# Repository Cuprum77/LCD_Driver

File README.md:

# LCD Driver Project

This repository contains my attempt at creating a "universal" driver board that fits most of the new 40 pin LCDs from China. These new LCDs all utilize a 40 pin flat flex cable, and utilize the ST7701 driver IC. 
This means that they are rather simple RGB devices, not too unlike the old VGA standard. 
The main goal however, is to have a board that does not require any system drivers, and utilize the standard connectors that are available on most SBCs, such as the Raspberry Pi, as well as most laptops and desktops.

## Table of contents
- [Supported LCDs](#supported-lcds)
- [Project layout](#project-layout)
- [License](#license)

## Supported LCDs

This table lists the LCDs that I have bought and tested with the driver board.

| Format | Size  | Resolution | Driver IC | Touch | Link      | Additional notes |
| ------ | ----- | ---------- | --------- | ----- | --------- | ---------------- |
| Bar    | 3.99" | 400x960    | ST7701    | Yes   | [AliExpress](https://www.aliexpress.com/item/1005005622337201.html) | |
| Square | 3.95" | 480x480    | ST7701    | Yes   | [AliExpress](https://www.aliexpress.com/item/1005005230886441.html) | NOT FULLY TESTED YET |

Alternatively, any other board that uses the ST7701 driver IC and with the following [pinout](./resources/PINOUT.md) should work with the driver board. However, you must generate a new ROM file for the FPGA.

## Project layout
- [UVVM_Light](https://github.com/UVVM/UVVM_Light) - The UVVM framework
- [bitfiles](bitfiles/) - FPGA bitfiles
- [edid](edid/) - EDID files for the LCDs
- [hardware](hardware/) - The KiCad project files for the driver boards
- [resources](resources/) - Resources for the project, such as datasheets
- [rom](rom/) - The ROM files for the FPGA projects
- [sim](sim/) - The UVVM testbenches for the driver boards
- [software](software/) - The software for the driver boards
- [vivado-library](https://github.com/Digilent/vivado-library/) - The Vivado library files for the driver boards

## License
This project is licensed under CERN Open Hardware License Version 2 - Strong Reciprocity (CERN-OHL-S-2.0). See [LICENSE](LICENSE) for more details.
Note that some files in this repository may be licensed under different licenses. Please check the respective files for more information.

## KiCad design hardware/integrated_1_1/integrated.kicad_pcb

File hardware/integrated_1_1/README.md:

# Integrated Solution Rev 1.1

## Introduction

Even smaller than the previous revision, this design is a complete redesign of the previous, and implements fixes for the critical errors in the previous design. This design is still in the prototype phase and is not ready for production.

This is a PCB that integrates everything needed to drive the display. It is designed to sit on the back of the display without interfering with the display frame. It is specifically designed for the pinout of the newer non-standard displays that have come out of China in the recent years. Specifically those that support the RGB666 interface.

This design utilizes a Spartan 6 FPGA to drive the display. This was chosen over dedicated ASICs due to cost and adaptability. This should allow me to add features such as a splash screen or other custom features that are not possible with a dedicated ASIC.

## Features
- Spartan 6 FPGA [^1]
- DVI Input [^2]
- RP2040 microcontroller
- USB-C [^3] [^4]
- Backlight driver with dimming control
- LCD connector

[^1]: XC6SLX9-TQG144
[^2]: The DVI input is over a HDMI-like connector. This is due to licensing issues with the HDMI standard that I cannot afford to pay for. Any reference to HDMI in this project is purely for the sake of simplicity and is not meant to imply that this project is HDMI compatible.
[^3]: Does not support PD.
[^4]: Limited to USB 1.1 speeds. This is limited by the RP2040 which handles the USB interface.

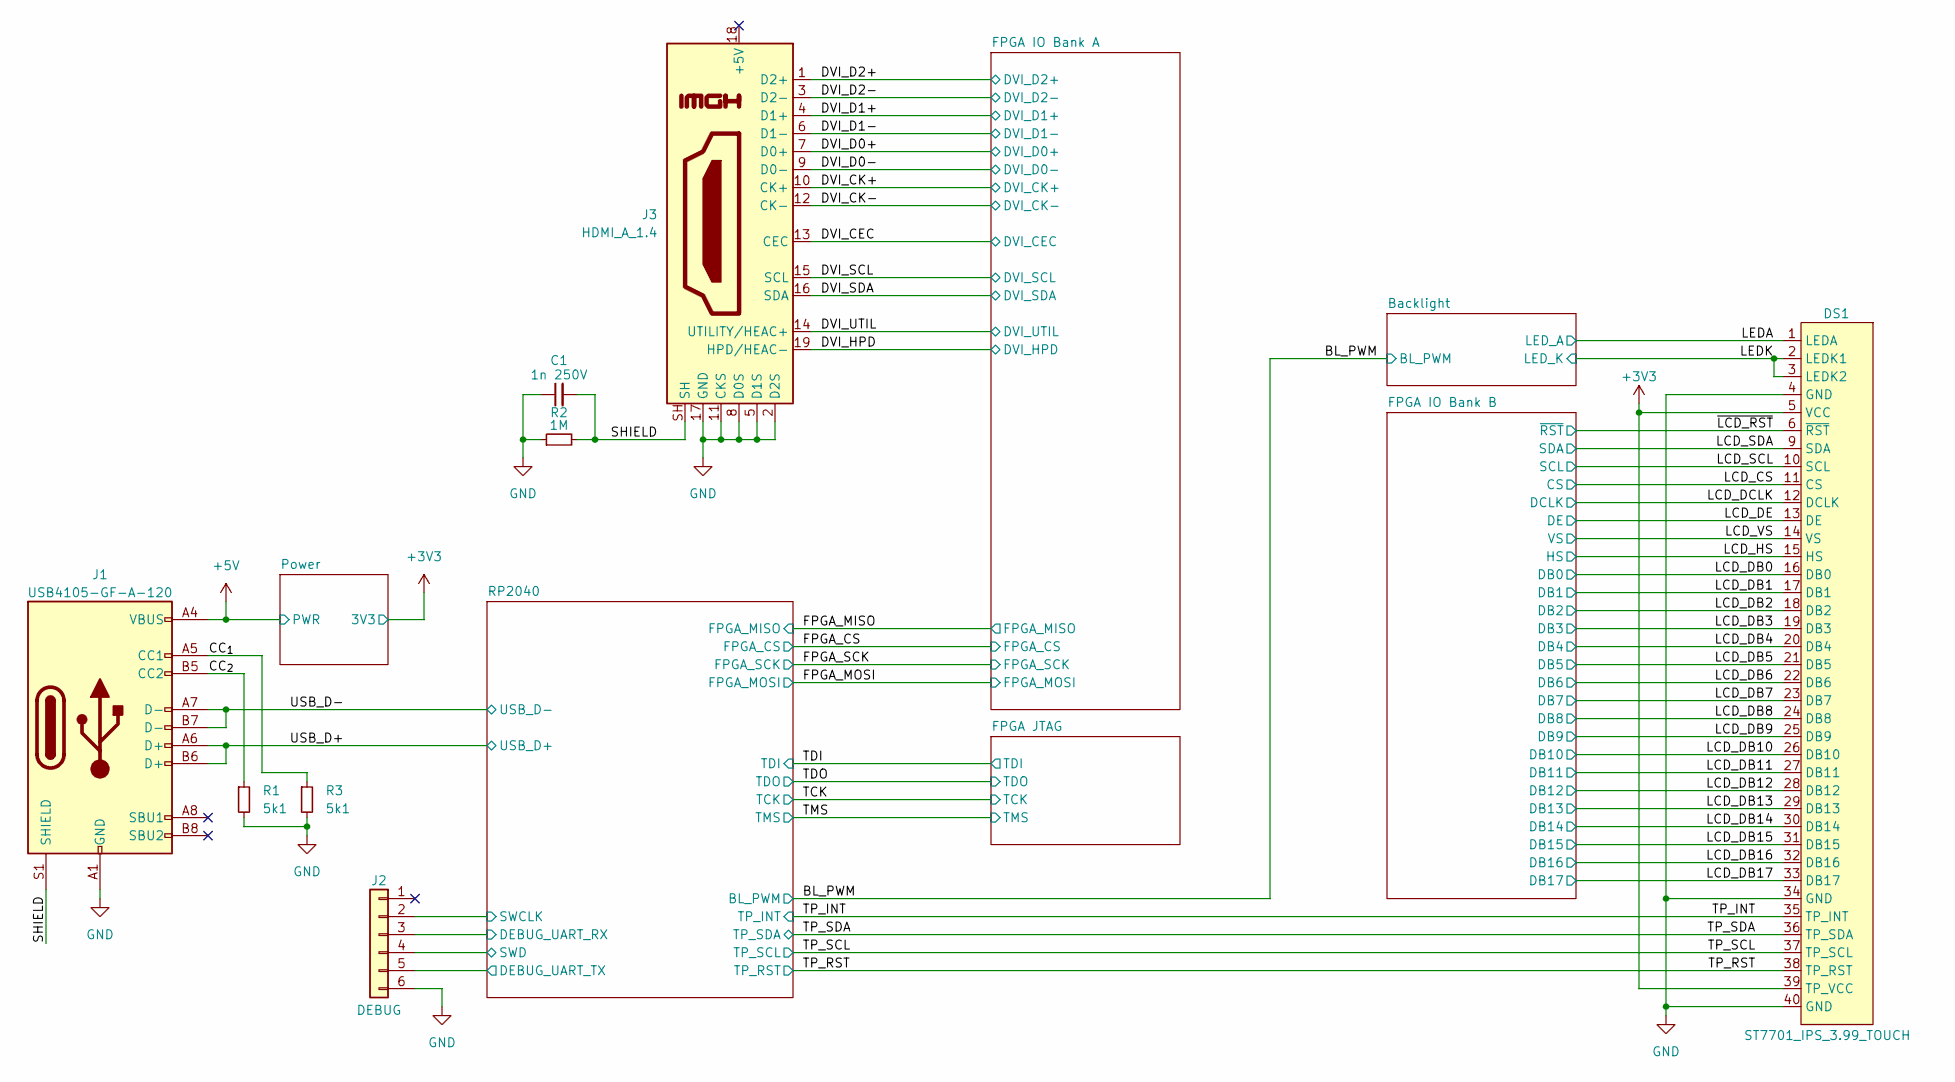
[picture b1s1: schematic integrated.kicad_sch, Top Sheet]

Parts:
C1: 1n 250V; C_0603_1608Metric
DS1: ST7701_IPS_3.99_TOUCH; GCT_FFC2B35-40-G_REVA2_INV
J1: USB4105-GF-A-120; CONN_217182-0001_MOL
J2: DEBUG; Paw-Connect_RevB_TC2030-IDC-NL_2x03_P1.27mm_Vertical
J3: HDMI_A_1.4; MOLEX_476591102
R1, R3: 5k1; R_0402_1005Metric
R2: 1M; R_0402_1005Metric

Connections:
+3V3: DS1.5 (VCC), DS1.39 (TP_VCC); also elsewhere on the board
+5V: J1.A4 (VBUS), J1.A9 (VBUS), J1.B4 (VBUS), J1.B9 (VBUS); also elsewhere on the board
/CC_{1}: J1.A5 (CC1), R3.1
/CC_{2}: J1.B5 (CC2), R1.1
/DVI_CEC: J3.13 (CEC); also elsewhere on the board
/DVI_CK+: J3.10 (CK+); also elsewhere on the board
/DVI_CK-: J3.12 (CK-); also elsewhere on the board
/DVI_D0+: J3.7 (D0+); also elsewhere on the board
/DVI_D0-: J3.9 (D0-); also elsewhere on the board
/DVI_D1+: J3.4 (D1+); also elsewhere on the board
/DVI_D1-: J3.6 (D1-); also elsewhere on the board
/DVI_D2+: J3.1 (D2+); also elsewhere on the board
/DVI_D2-: J3.3 (D2-); also elsewhere on the board
/DVI_HPD: J3.19 (HPD/HEAC-); also elsewhere on the board
/DVI_SCL: J3.15 (SCL); also elsewhere on the board
/DVI_SDA: J3.16 (SDA); also elsewhere on the board
/LCD_CS: DS1.11 (CS); also elsewhere on the board
/LCD_DB0: DS1.16 (DB0); also elsewhere on the board
/LCD_DB1: DS1.17 (DB1); also elsewhere on the board
/LCD_DB2: DS1.18 (DB2); also elsewhere on the board
/LCD_DB3: DS1.19 (DB3); also elsewhere on the board
/LCD_DB4: DS1.20 (DB4); also elsewhere on the board
/LCD_DB5: DS1.21 (DB5); also elsewhere on the board
/LCD_DB6: DS1.22 (DB6); also elsewhere on the board
/LCD_DB7: DS1.23 (DB7); also elsewhere on the board
/LCD_DB8: DS1.24 (DB8); also elsewhere on the board
/LCD_DB9: DS1.25 (DB9); also elsewhere on the board
/LCD_DB10: DS1.26 (DB10); also elsewhere on the board
/LCD_DB11: DS1.27 (DB11); also elsewhere on the board
/LCD_DB12: DS1.28 (DB12); also elsewhere on the board
/LCD_DB13: DS1.29 (DB13); also elsewhere on the board
/LCD_DB14: DS1.30 (DB14); also elsewhere on the board
/LCD_DB15: DS1.31 (DB15); also elsewhere on the board
/LCD_DB16: DS1.32 (DB16); also elsewhere on the board
/LCD_DB17: DS1.33 (DB17); also elsewhere on the board
/LCD_DCLK: DS1.12 (DCLK); also elsewhere on the board
/LCD_DE: DS1.13 (DE); also elsewhere on the board
/LCD_HS: DS1.15 (HS); also elsewhere on the board
/LCD_SCL: DS1.10 (SCL); also elsewhere on the board
/LCD_SDA: DS1.9 (SDA); also elsewhere on the board
/LCD_VS: DS1.14 (VS); also elsewhere on the board
/LEDA: DS1.1 (LEDA); also elsewhere on the board
/LEDK: DS1.2 (LEDK1), DS1.3 (LEDK2); also elsewhere on the board
/RP2040/DEBUG_UART_RX: J2.3; also elsewhere on the board
/RP2040/DEBUG_UART_TX: J2.5; also elsewhere on the board
/RP2040/SWCLK: J2.2; also elsewhere on the board
/RP2040/SWD: J2.4; also elsewhere on the board
/SHIELD: C1.2, J1.S1 (SHIELD), J3.SH, J3.SH1 (SH), J3.SH2 (SH), J3.SH3 (SH), R2.2
/TP_INT: DS1.35 (TP_INT); also elsewhere on the board
/TP_RST: DS1.38 (TP_RST); also elsewhere on the board
/TP_SCL: DS1.37 (TP_SCL); also elsewhere on the board
/TP_SDA: DS1.36 (TP_SDA); also elsewhere on the board
/USB_D+: J1.A6 (D+), J1.B6 (D+); also elsewhere on the board
/USB_D-: J1.A7 (D-), J1.B7 (D-); also elsewhere on the board
/~LCD_RST: DS1.6 (~RST); also elsewhere on the board
GND: C1.1, DS1.4 (GND), DS1.34 (GND), DS1.40 (GND), DS1.S1 (GND), DS1.S2 (GND), J1.A1 (GND), J1.A12 (GND), J1.B1 (GND), J1.B12 (GND), J2.6, J3.2 (D2S), J3.5 (D1S), J3.8 (D0S), J3.11 (CKS), J3.14 (UTILITY/HEAC+), J3.17 (GND), R1.2, R2.1, R3.2; also elsewhere on the board

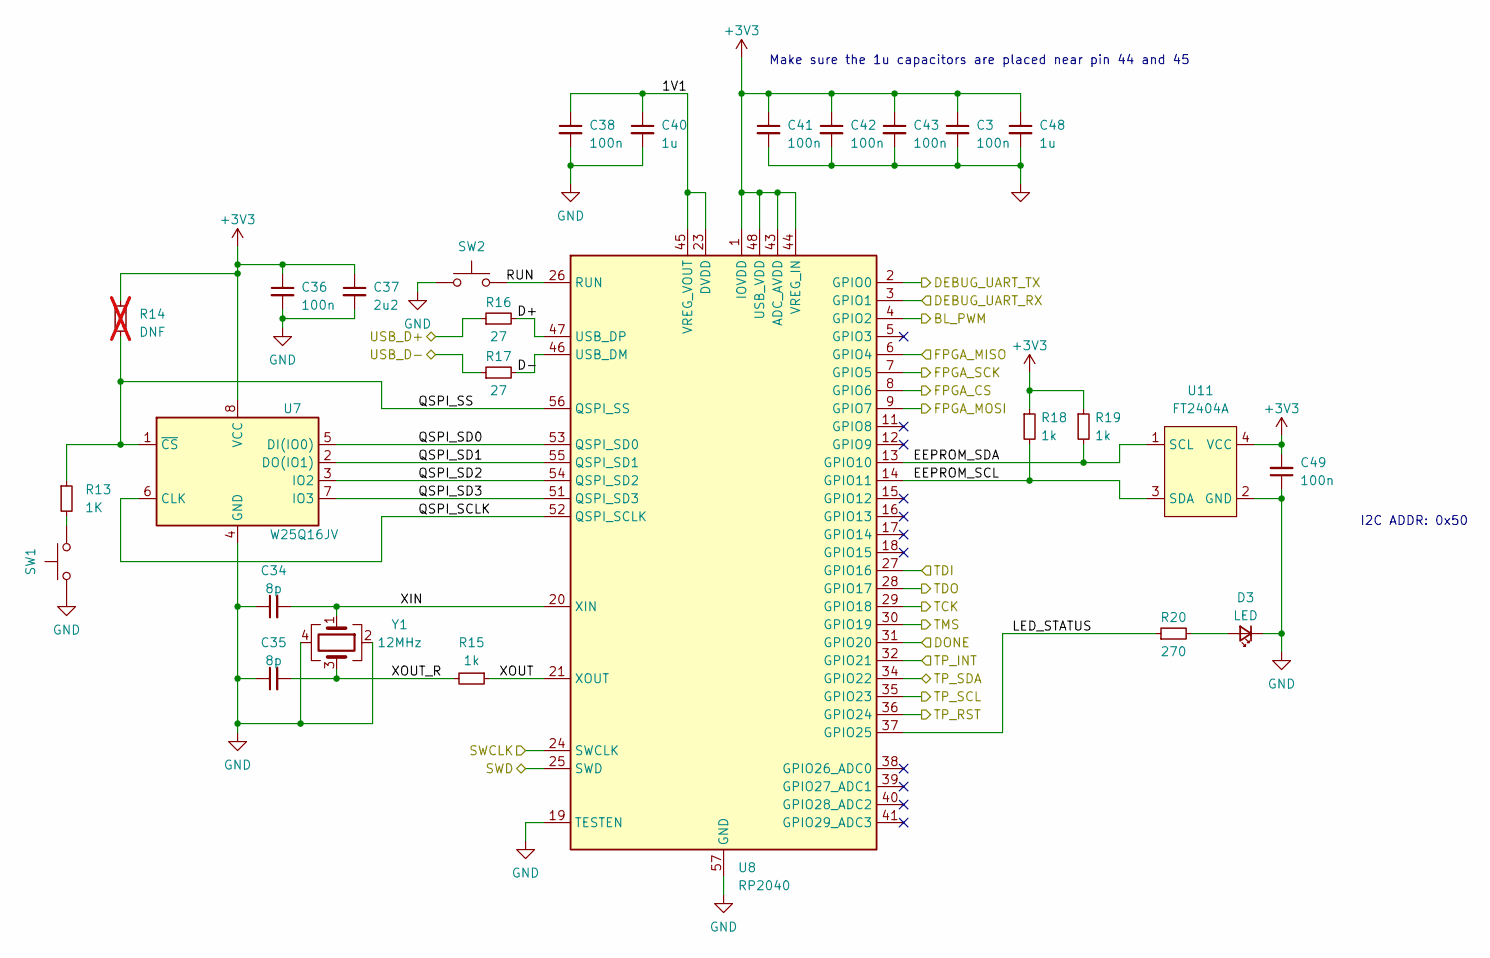
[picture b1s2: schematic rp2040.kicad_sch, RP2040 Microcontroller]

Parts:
C3, C36, C38, C41, C42, C43, C49: 100n; C_0402_1005Metric
C34, C35: 8p; C_0402_1005Metric
C37: 2u2; C_0402_1005Metric
C40, C48: 1u; C_0402_1005Metric
D3: LED; D_0805_2012Metric
R13: 1K; R_0402_1005Metric
R14: DNF; R_0402_1005Metric; not fitted
R15, R18, R19: 1k; R_0402_1005Metric
R16, R17: 27; R_0402_1005Metric
R20: 270; R_0402_1005Metric
SW1, SW2: DNF; PTS636 SM25J SMTR LFS
U7: W25Q16JV; W25Q16JVUXIQ TR
U8: RP2040; QFN-56-1EP_7x7mm_P0.4mm_EP3.2x3.2mm
U11: FT2404A; SOT-23-5
Y1: 12MHz; ECS120836CKMTR3

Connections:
+3V3: C3.1, C36.1, C37.1, C41.1, C42.1, C43.1, C48.1, C49.2, R14.2, R18.1, R19.1, U7.8 (VCC), U8.1 (IOVDD), U8.10 (IOVDD), U8.22 (IOVDD), U8.33 (IOVDD), U8.42 (IOVDD), U8.43 (ADC_AVDD), U8.44 (VREG_IN), U8.48 (USB_VDD), U8.49 (IOVDD), U11.4 (VCC); also elsewhere on the board
/BL_PWM: U8.4 (GPIO2); also elsewhere on the board
/FPGA_CS: U8.8 (GPIO6); also elsewhere on the board
/FPGA_MISO: U8.6 (GPIO4); also elsewhere on the board
/FPGA_MOSI: U8.9 (GPIO7); also elsewhere on the board
/FPGA_SCK: U8.7 (GPIO5); also elsewhere on the board
/RP2040/1V1: C38.1, C40.1, U8.23 (DVDD), U8.45 (VREG_VOUT), U8.50 (DVDD)
/RP2040/D+: R16.2, U8.47 (USB_DP)
/RP2040/D-: R17.2, U8.46 (USB_DM)
/RP2040/DEBUG_UART_RX: U8.3 (GPIO1); also elsewhere on the board
/RP2040/DEBUG_UART_TX: U8.2 (GPIO0); also elsewhere on the board
/RP2040/DONE: U8.31 (GPIO20)
/RP2040/EEPROM_SCL: R18.2, U8.14 (GPIO11), U11.3 (SDA)
/RP2040/EEPROM_SDA: R19.2, U8.13 (GPIO10), U11.1 (SCL)
/RP2040/LED_STATUS: R20.1, U8.37 (GPIO25)
/RP2040/QSPI_SCLK: U7.6 (CLK), U8.52 (QSPI_SCLK)
/RP2040/QSPI_SD0: U7.5 (DI(IO0)), U8.53 (QSPI_SD0)
/RP2040/QSPI_SD1: U7.2 (DO(IO1)), U8.55 (QSPI_SD1)
/RP2040/QSPI_SD2: U7.3 (IO2), U8.54 (QSPI_SD2)
/RP2040/QSPI_SD3: U7.7 (IO3), U8.51 (QSPI_SD3)
/RP2040/QSPI_SS: R13.1, R14.1, U7.1 (~CS), U8.56 (QSPI_SS)
/RP2040/RUN: SW2.2, U8.26 (RUN)
/RP2040/SWCLK: U8.24 (SWCLK); also elsewhere on the board
/RP2040/SWD: U8.25 (SWD); also elsewhere on the board
/RP2040/XIN: C34.2, U8.20 (XIN), Y1.1
/RP2040/XOUT: R15.1, U8.21 (XOUT)
/RP2040/XOUT_R: C35.2, R15.2, Y1.3
/TCK: U8.29 (GPIO18); also elsewhere on the board
/TDI: U8.27 (GPIO16); also elsewhere on the board
/TDO: U8.28 (GPIO17); also elsewhere on the board
/TMS: U8.30 (GPIO19); also elsewhere on the board
/TP_INT: U8.32 (GPIO21); also elsewhere on the board
/TP_RST: U8.36 (GPIO24); also elsewhere on the board
/TP_SCL: U8.35 (GPIO23); also elsewhere on the board
/TP_SDA: U8.34 (GPIO22); also elsewhere on the board
/USB_D+: R16.1; also elsewhere on the board
/USB_D-: R17.1; also elsewhere on the board
GND: C3.2, C34.1, C35.1, C36.2, C37.2, C38.2, C40.2, C41.2, C42.2, C43.2, C48.2, C49.1, D3.1 (K), SW1.1, SW2.1, U7.4 (GND), U7.9 (GND), U8.19 (TESTEN), U8.57 (GND), U11.2 (GND), Y1.2, Y1.4; also elsewhere on the board
unnamed: D3.2 (A), R20.2
unnamed: R13.2, SW1.2

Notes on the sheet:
I2C ADDR: 0x50
Make sure the 1u capacitors are placed near pin 44 and 45

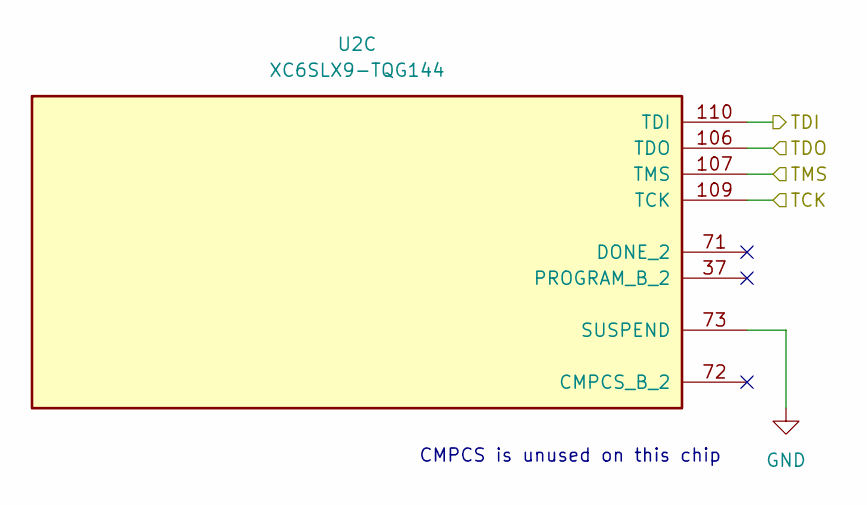
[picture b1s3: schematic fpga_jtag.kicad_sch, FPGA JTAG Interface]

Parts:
U2: XC6SLX9-TQG144; TQFP-144_20x20mm_P0.5mm

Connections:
/TCK: U2.109 (TCK); also elsewhere on the board
/TDI: U2.110 (TDI); also elsewhere on the board
/TDO: U2.106 (TDO); also elsewhere on the board
/TMS: U2.107 (TMS); also elsewhere on the board
GND: U2.73 (SUSPEND); also elsewhere on the board

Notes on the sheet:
CMPCS is unused on this chip

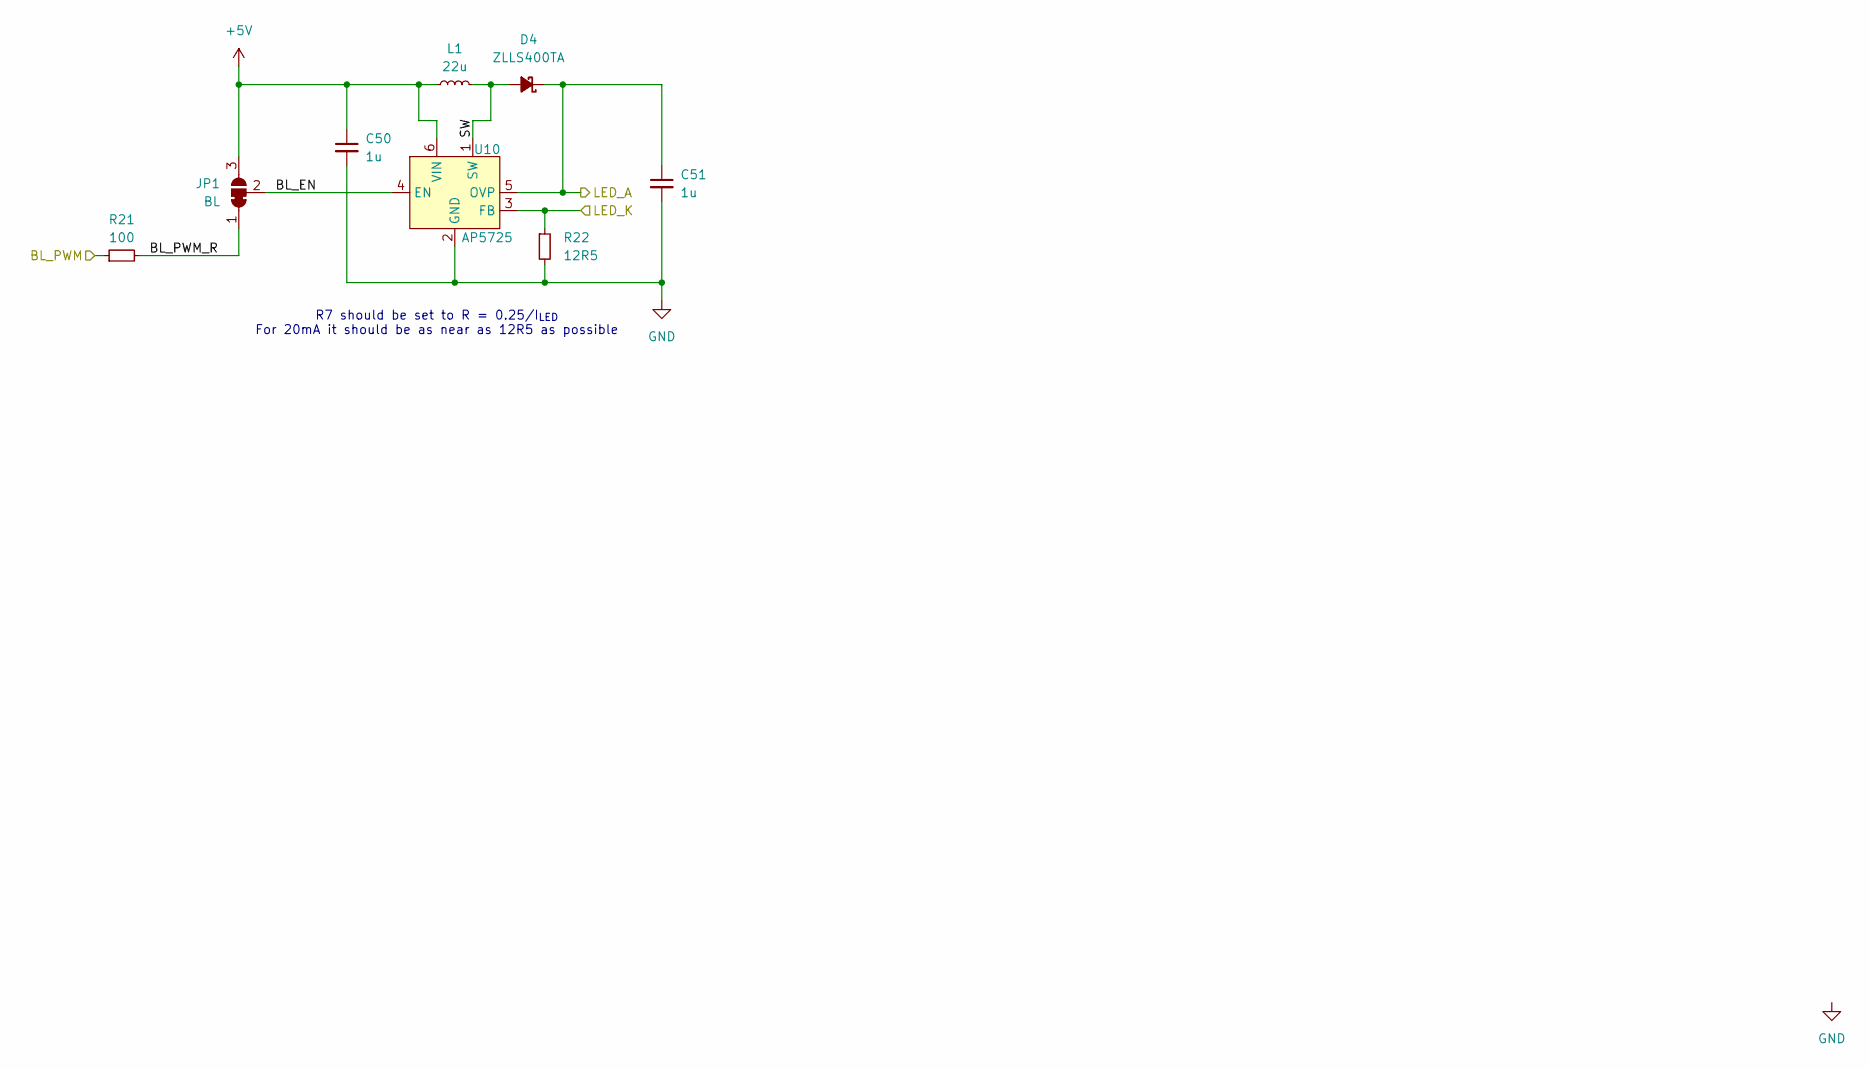
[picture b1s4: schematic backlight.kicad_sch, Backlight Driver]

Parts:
C50: 1u; C_0402_1005Metric
C51: 1u; C_0603_1608Metric
D4: ZLLS400TA; D_SOD-323
JP1: BL; SolderJumper-3_P1.3mm_Bridged12_RoundedPad1.0x1.5mm
L1: 22u; XRNR4012
R21: 100; R_0402_1005Metric
R22: 12R5; R_0603_1608Metric
U10: AP5725; SOT-23-6

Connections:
+5V: C50.1, JP1.3 (B), L1.1, U10.6 (VIN); also elsewhere on the board
/BL_PWM: R21.1; also elsewhere on the board
/Backlight/BL_EN: JP1.2 (C), U10.4 (EN)
/Backlight/BL_PWM_R: JP1.1 (A), R21.2
/Backlight/SW: D4.2 (A), L1.2, U10.1 (SW)
/LEDA: C51.1, D4.1 (K), U10.5 (OVP); also elsewhere on the board
/LEDK: R22.1, U10.3 (FB); also elsewhere on the board
GND: C50.2, C51.2, R22.2, U10.2 (GND); also elsewhere on the board

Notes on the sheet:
R7 should be set to R = 0.25/I_{LED} For 20mA it should be as near as 12R5 as possible

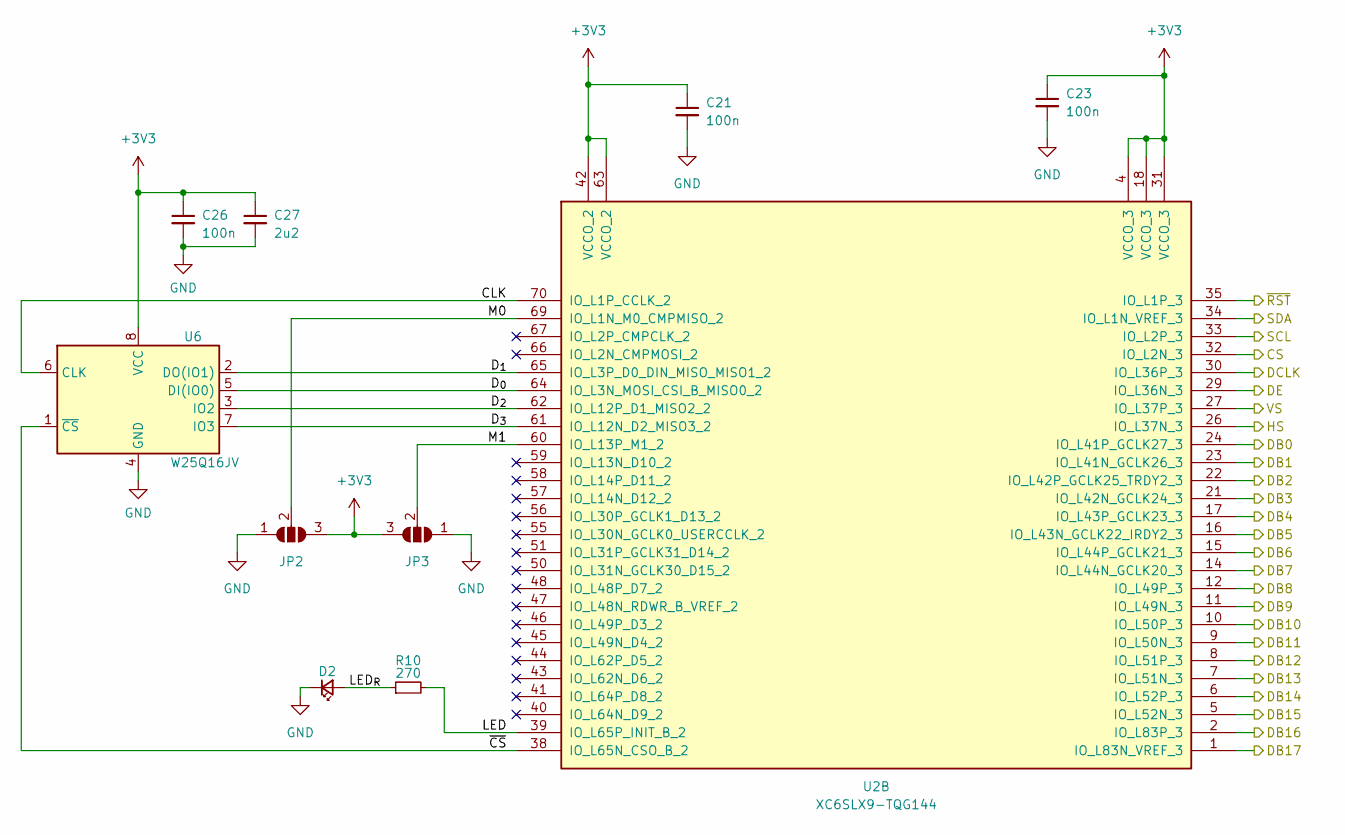
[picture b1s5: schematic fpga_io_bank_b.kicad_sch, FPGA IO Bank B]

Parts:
C21, C23, C26: 100n; C_0402_1005Metric
C27: 2u2; C_0402_1005Metric
D2: LED; D_0805_2012Metric
JP2, JP3: SolderJumper_3_Open; SolderJumper-3_P1.3mm_Open_RoundedPad1.0x1.5mm
R10: 270; R_0402_1005Metric
U2: XC6SLX9-TQG144; TQFP-144_20x20mm_P0.5mm
U6: W25Q16JV; W25Q16JVUXIQ TR

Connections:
+3V3: C21.1, C23.1, C26.1, C27.1, JP2.3 (B), JP3.3 (B), U2.4 (VCCO_3), U2.18 (VCCO_3), U2.31 (VCCO_3), U2.42 (VCCO_2), U2.63 (VCCO_2), U6.8 (VCC); also elsewhere on the board
/FPGA IO Bank B/CLK: U2.70 (IO_L1P_CCLK_2), U6.6 (CLK)
/FPGA IO Bank B/D_{0}: U2.64 (IO_L3N_MOSI_CSI_B_MISO0_2), U6.5 (DI(IO0))
/FPGA IO Bank B/D_{1}: U2.65 (IO_L3P_D0_DIN_MISO_MISO1_2), U6.2 (DO(IO1))
/FPGA IO Bank B/D_{2}: U2.62 (IO_L12P_D1_MISO2_2), U6.3 (IO2)
/FPGA IO Bank B/D_{3}: U2.61 (IO_L12N_D2_MISO3_2), U6.7 (IO3)
/FPGA IO Bank B/LED: R10.2, U2.39 (IO_L65P_INIT_B_2)
/FPGA IO Bank B/LED_{R}: D2.2 (A), R10.1
/FPGA IO Bank B/M0: JP2.2 (C), U2.69 (IO_L1N_M0_CMPMISO_2)
/FPGA IO Bank B/M1: JP3.2 (C), U2.60 (IO_L13P_M1_2)
/FPGA IO Bank B/~CS: U2.38 (IO_L65N_CSO_B_2), U6.1 (~CS)
/LCD_CS: U2.32 (IO_L2N_3); also elsewhere on the board
/LCD_DB0: U2.24 (IO_L41P_GCLK27_3); also elsewhere on the board
/LCD_DB1: U2.23 (IO_L41N_GCLK26_3); also elsewhere on the board
/LCD_DB2: U2.22 (IO_L42P_GCLK25_TRDY2_3); also elsewhere on the board
/LCD_DB3: U2.21 (IO_L42N_GCLK24_3); also elsewhere on the board
/LCD_DB4: U2.17 (IO_L43P_GCLK23_3); also elsewhere on the board
/LCD_DB5: U2.16 (IO_L43N_GCLK22_IRDY2_3); also elsewhere on the board
/LCD_DB6: U2.15 (IO_L44P_GCLK21_3); also elsewhere on the board
/LCD_DB7: U2.14 (IO_L44N_GCLK20_3); also elsewhere on the board
/LCD_DB8: U2.12 (IO_L49P_3); also elsewhere on the board
/LCD_DB9: U2.11 (IO_L49N_3); also elsewhere on the board
/LCD_DB10: U2.10 (IO_L50P_3); also elsewhere on the board
/LCD_DB11: U2.9 (IO_L50N_3); also elsewhere on the board
/LCD_DB12: U2.8 (IO_L51P_3); also elsewhere on the board
/LCD_DB13: U2.7 (IO_L51N_3); also elsewhere on the board
/LCD_DB14: U2.6 (IO_L52P_3); also elsewhere on the board
/LCD_DB15: U2.5 (IO_L52N_3); also elsewhere on the board
/LCD_DB16: U2.2 (IO_L83P_3); also elsewhere on the board
/LCD_DB17: U2.1 (IO_L83N_VREF_3); also elsewhere on the board
/LCD_DCLK: U2.30 (IO_L36P_3); also elsewhere on the board
/LCD_DE: U2.29 (IO_L36N_3); also elsewhere on the board
/LCD_HS: U2.26 (IO_L37N_3); also elsewhere on the board
/LCD_SCL: U2.33 (IO_L2P_3); also elsewhere on the board
/LCD_SDA: U2.34 (IO_L1N_VREF_3); also elsewhere on the board
/LCD_VS: U2.27 (IO_L37P_3); also elsewhere on the board
/~LCD_RST: U2.35 (IO_L1P_3); also elsewhere on the board
GND: C21.2, C23.2, C26.2, C27.2, D2.1 (K), JP2.1 (A), JP3.1 (A), U6.4 (GND), U6.9 (GND); also elsewhere on the board

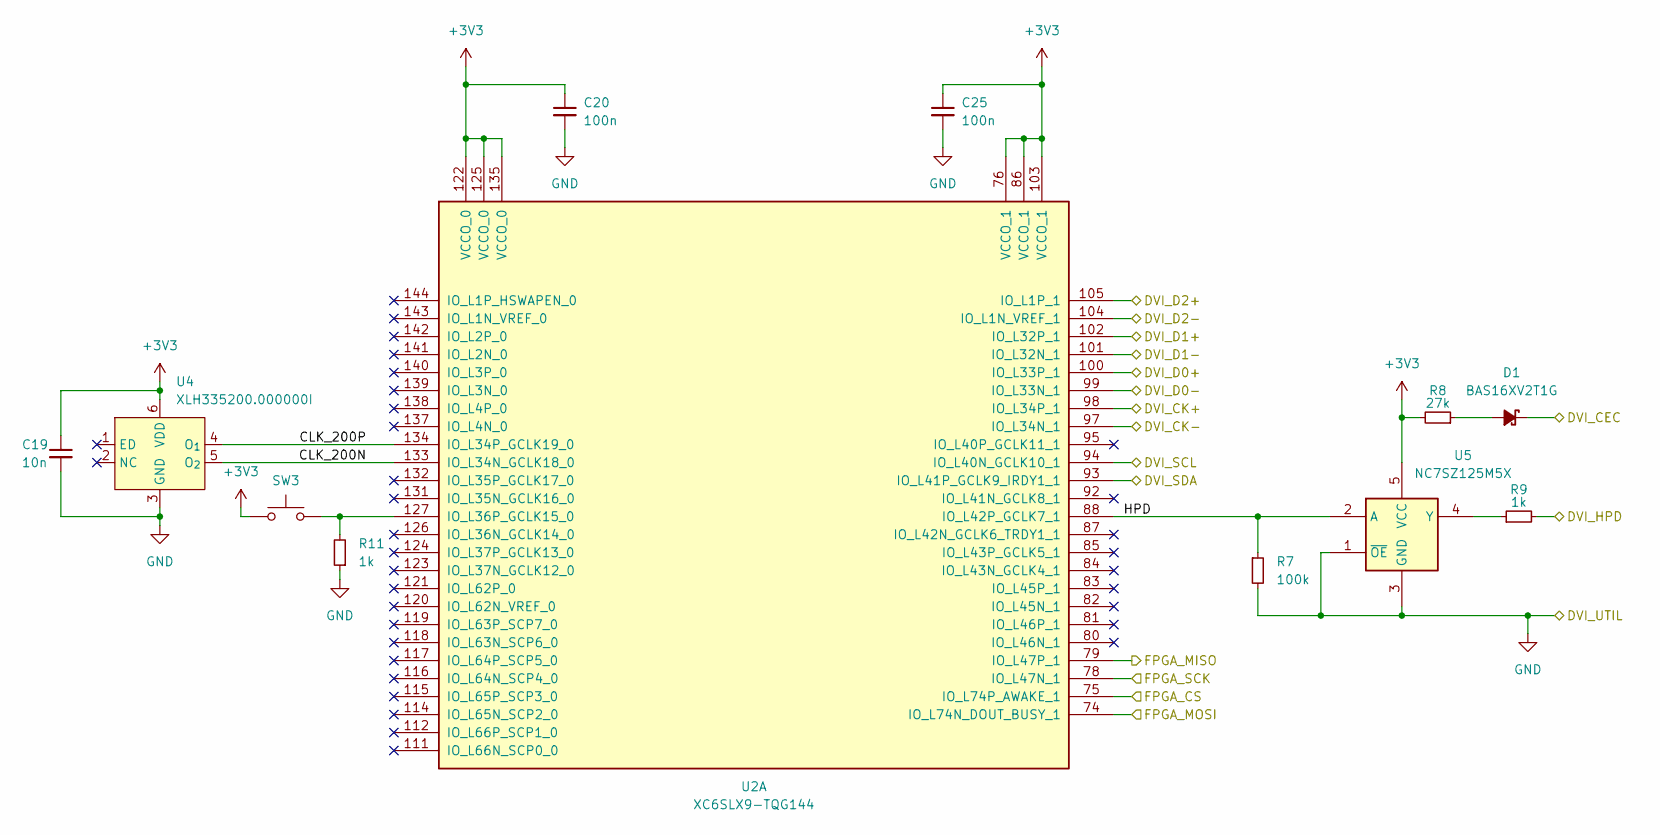
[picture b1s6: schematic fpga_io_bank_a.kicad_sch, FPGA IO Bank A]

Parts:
C19: 10n; C_0402_1005Metric
C20, C25: 100n; C_0402_1005Metric
D1: BAS16XV2T1G; D_SOD-523
R7: 100k; R_0402_1005Metric
R8: 27k; R_0402_1005Metric
R9, R11: 1k; R_0402_1005Metric
SW3: DNF; PTS636 SM25J SMTR LFS
U2: XC6SLX9-TQG144; TQFP-144_20x20mm_P0.5mm
U4: XLH335200.000000I
U5: NC7SZ125M5X; SOT-23-5

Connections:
+3V3: C19.1, C20.1, C25.1, R8.2, SW3.1, U2.76 (VCCO_1), U2.86 (VCCO_1), U2.103 (VCCO_1), U2.122 (VCCO_0), U2.125 (VCCO_0), U2.135 (VCCO_0), U4.6 (VDD), U5.5 (VCC); also elsewhere on the board
/DVI_CEC: D1.1 (K); also elsewhere on the board
/DVI_CK+: U2.98 (IO_L34P_1); also elsewhere on the board
/DVI_CK-: U2.97 (IO_L34N_1); also elsewhere on the board
/DVI_D0+: U2.100 (IO_L33P_1); also elsewhere on the board
/DVI_D0-: U2.99 (IO_L33N_1); also elsewhere on the board
/DVI_D1+: U2.102 (IO_L32P_1); also elsewhere on the board
/DVI_D1-: U2.101 (IO_L32N_1); also elsewhere on the board
/DVI_D2+: U2.105 (IO_L1P_1); also elsewhere on the board
/DVI_D2-: U2.104 (IO_L1N_VREF_1); also elsewhere on the board
/DVI_HPD: R9.2; also elsewhere on the board
/DVI_SCL: U2.94 (IO_L40N_GCLK10_1); also elsewhere on the board
/DVI_SDA: U2.93 (IO_L41P_GCLK9_IRDY1_1); also elsewhere on the board
/FPGA IO Bank A/CLK_200N: U2.133 (IO_L34N_GCLK18_0), U4.5 (O_{2})
/FPGA IO Bank A/CLK_200P: U2.134 (IO_L34P_GCLK19_0), U4.4 (O_{1})
/FPGA IO Bank A/HPD: R7.1, U2.88 (IO_L42P_GCLK7_1), U5.2 (A)
/FPGA_CS: U2.75 (IO_L74P_AWAKE_1); also elsewhere on the board
/FPGA_MISO: U2.79 (IO_L47P_1); also elsewhere on the board
/FPGA_MOSI: U2.74 (IO_L74N_DOUT_BUSY_1); also elsewhere on the board
/FPGA_SCK: U2.78 (IO_L47N_1); also elsewhere on the board
GND: C19.2, C20.2, C25.2, R7.2, R11.1, U4.3 (GND), U5.1 (~OE), U5.3 (GND); also elsewhere on the board
unnamed: D1.2 (A), R8.1
unnamed: R11.2, SW3.2, U2.127 (IO_L36P_GCLK15_0)
unnamed: R9.1, U5.4 (Y)

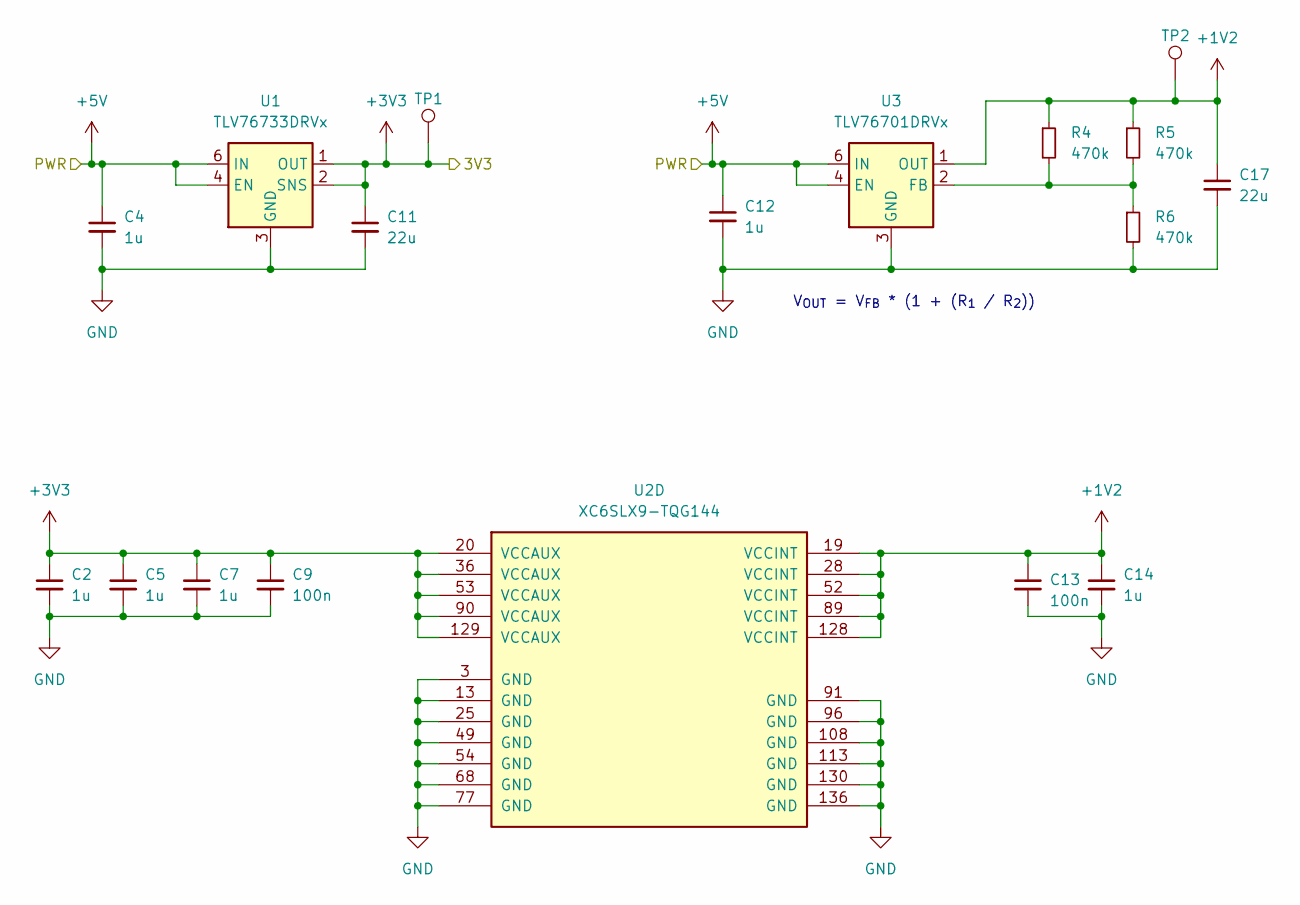
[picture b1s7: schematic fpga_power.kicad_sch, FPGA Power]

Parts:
C2, C4, C5, C7, C12, C14: 1u; C_0402_1005Metric
C9, C13: 100n; C_0402_1005Metric
C11, C17: 22u; C_0603_1608Metric
R4, R5, R6: 470k; R_0402_1005Metric
TP1, TP2: TestPoint; TestPoint_Pad_D1.0mm
U1: TLV76733DRVx; WSON-6-1EP_2x2mm_P0.65mm_EP1x1.6mm_ThermalVias
U2: XC6SLX9-TQG144; TQFP-144_20x20mm_P0.5mm
U3: TLV76701DRVx; WSON-6-1EP_2x2mm_P0.65mm_EP1x1.6mm_ThermalVias

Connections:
+1V2: C13.1, C14.1, C17.1, R4.1, R5.1, TP2.1, U2.19 (VCCINT), U2.28 (VCCINT), U2.52 (VCCINT), U2.89 (VCCINT), U2.128 (VCCINT), U3.1 (OUT)
+3V3: C2.1, C5.1, C7.1, C9.1, C11.1, TP1.1, U1.1 (OUT), U1.2 (SNS), U2.20 (VCCAUX), U2.36 (VCCAUX), U2.53 (VCCAUX), U2.90 (VCCAUX), U2.129 (VCCAUX); also elsewhere on the board
+5V: C4.1, C12.1, U1.4 (EN), U1.6 (IN), U3.4 (EN), U3.6 (IN); also elsewhere on the board
GND: C2.2, C4.2, C5.2, C7.2, C9.2, C11.2, C12.2, C13.2, C14.2, C17.2, R6.2, U1.3 (GND), U1.5 (GND), U1.7 (PAD), U2.3 (GND), U2.13 (GND), U2.25 (GND), U2.49 (GND), U2.54 (GND), U2.68 (GND), U2.77 (GND), U2.91 (GND), U2.96 (GND), U2.108 (GND), U2.113 (GND), U2.130 (GND), U2.136 (GND), U3.3 (GND), U3.5 (GND), U3.7 (PAD); also elsewhere on the board
unnamed: R4.2, R5.2, R6.1, U3.2 (FB)

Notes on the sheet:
V_{OUT} = V_{FB} * (1 + (R_{1} / R_{2}))

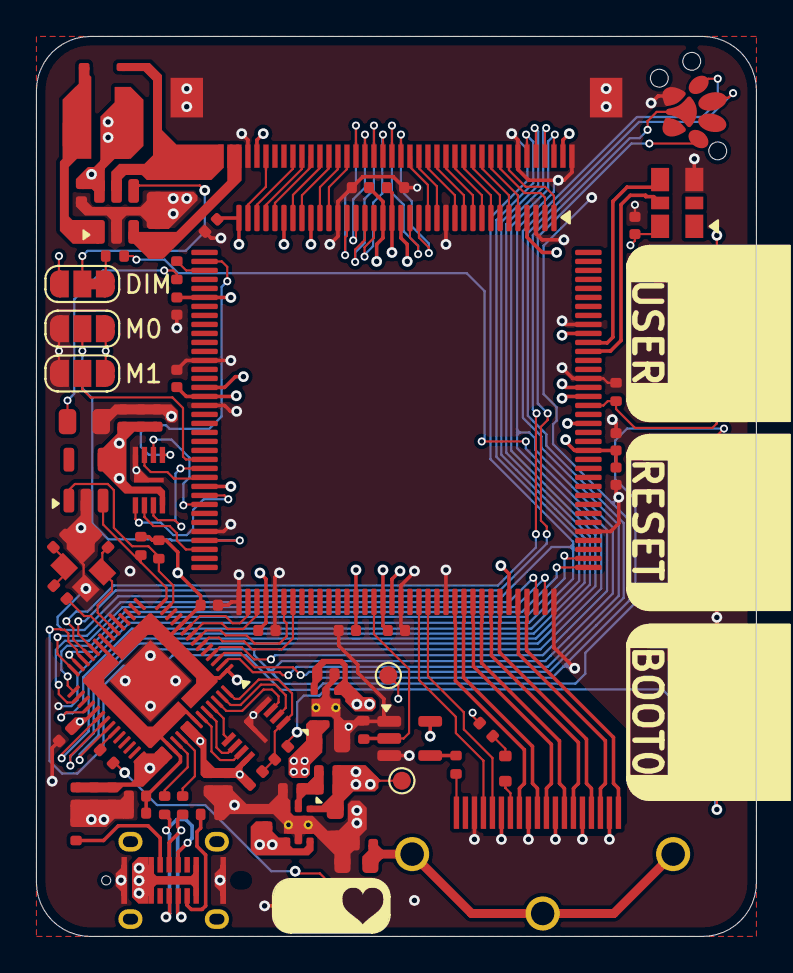
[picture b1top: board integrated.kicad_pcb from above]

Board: 4 copper layers, 40.0 x 50.0 mm, 81 parts (0 on the bottom side), 104 nets.
